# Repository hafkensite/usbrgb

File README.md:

# usbrgb

ATtiny85 based USB PCB that provides two WS2812B LED's, to be used as indicators.

# Hardware

The pcb design is based upon that of the [Digispark USB development board](http://digistump.com/products/1). For which they have released the [Eagle](https://s3.amazonaws.com/digistump-resources/files/3a5187f5_digispark_sources.zip) files.

The Digispark board uses an attiny84 microprocessor, which (with the help of some special software), can be programmed over USB once the bootloader is flashed once.

The width of the original Digispark pcb is slightly too wide to fit in some usb ports, when they are located at an edge. A fairly large part of the pcb is occupied by a voltage regulator. As the usbrgb PCB is to be used in a computer, there is no need for a 5Volt regulator.

Removing the regulator, and a few other non-critical components allowed the board to be narrower. I chose for a 'bigger' package for the passive components, as I want to solder it to manually.

## Layout

## Components

| Qty | Value      | Package | Parts  | Description                     |
| --- | ---------- | ------- | ------ | ------------------------------- |
| 1   | ATTINY85   | SOP8    | IC1    | Atmel ATTINY85-20SU             |
| 2   | 68R        | 1206    | R1, R2 | Resistor                        |
| 1   | 1K5        | 1206    | R3     | Resistor                        |
| 2   | 3.3v Zener | SOD-123 | D1, D2 | Diode                           |
| 1   | 4.7uf      | C1206   | C2     | Capacitor                       |
| 2   | WS2812B    | WS2812B | D3, D4 | WS2812B SMD addressable RGB LED |

# Embedded software

## Micronucleus bootloader
The [micronucleus](https://github.com/micronucleus/micronucleus) bootloader allows the Arduino IDE to program the chip over USB.

When the chip boots, it first presents itself as a usb device that can be programmed. After a short timeout the bootloader starts the Arduino code.

To flash the micronucleus bootloader you can use [avrdude](https://www.nongnu.org/avrdude/). I have programmed mine using an Arduino uno with the ISP sketch written to it.

## Arduino

To program the device using Arduino you can follow the steps describe in the [tutorial](http://digistump.com/wiki/digispark/tutorials/connecting).

> Note that the latest micronucleus version currently available (v2.04) is not supported by the Arduino plugin. I replaced the micronucleus application with the [latest version](https://github.com/micronucleus/micronucleus/tree/master/commandline), which works fine.

# Host software

The host application is written in Go, and uses the libusb interface to send control messages to the HID device. 

## Native messaging
The goal of this project is to be able to give a notification from within a browser. One of the ways to communicate from a browser to the host is using [native messaging](https://developer.mozilla.org/en-US/docs/Mozilla/Add-ons/WebExtensions/Native_messaging). This allows extensions to send messages to an executable on the host.

## Browser integration
The included firefox extension, together with the native-messaging application, allows the LED's to be set from within a web-page.

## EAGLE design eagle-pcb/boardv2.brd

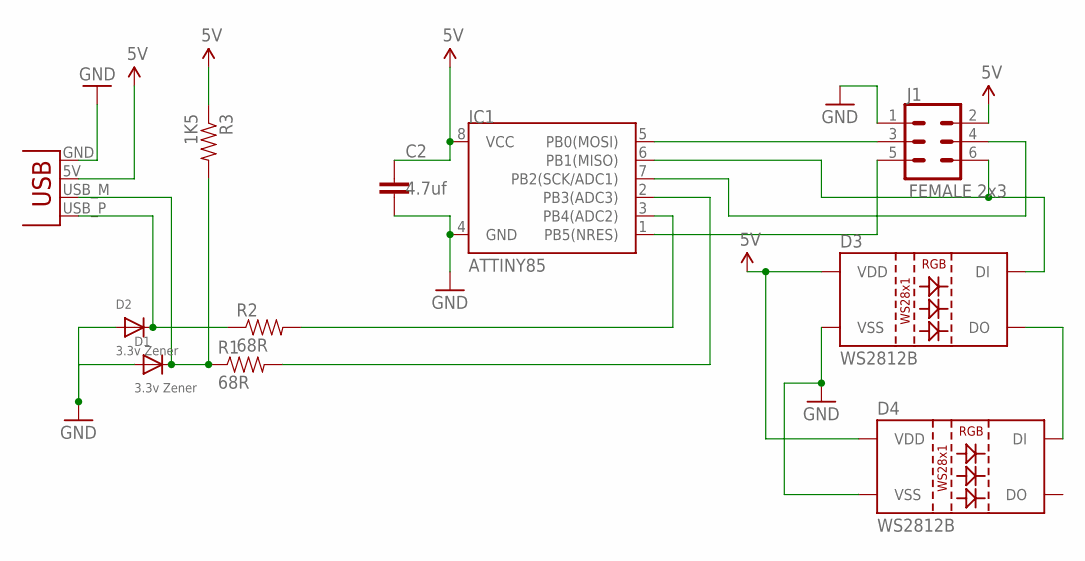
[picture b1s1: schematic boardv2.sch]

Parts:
C2: 4.7uf; C1206
D1, D2: 3.3v Zener; SOD-123
D3, D4: WS2812B
IC1: ATTINY85; SO08-EIAJ
J1: FEMALE 2x3; 2X3
R1, R2: 68R; 1206
R3: 1K5; 1206
X1: USBPCB; USB-A-PCB

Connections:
5V: C2.1, D3.1 (VDD), D4.1 (VDD), IC1.8 (VCC), J1.2, R3.1, X1.5V (VBUS)
GND: C2.2, D1.A, D2.A, D3.3 (VSS), D4.3 (VSS), IC1.4 (GND), J1.1, X1.GND
MISO: D3.4 (DI), IC1.6 (PB1(MISO)), J1.6
unnamed: D3.2 (DO), D4.4 (DI)
RESET: IC1.1 (PB5(NRES)), J1.5
SCK: IC1.7 (PB2(SCK/ADC1)), J1.4
SDA/MOSI: IC1.5 (PB0(MOSI)), J1.3
USB+: IC1.2 (PB3(ADC3)), R1.2
USB-: IC1.3 (PB4(ADC2)), R2.2
USB-M: D1.C, R1.1, R3.2, X1.USB_M (D-)
USB-P: D2.C, R2.1, X1.USB_P (D+)

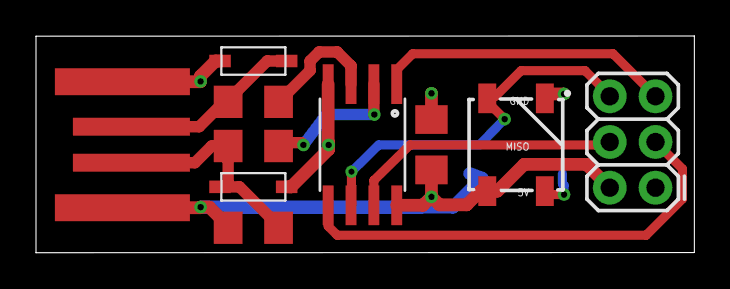
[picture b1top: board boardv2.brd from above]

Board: 2 copper layers, 36.6 x 12.0 mm, 11 parts (1 on the bottom side), 11 nets.

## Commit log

2020-07-26 Added eagle pcb files v1
2020-07-26 Added go app for browser native messaging
2020-07-26 Added arduino code for serial emulator
2020-07-26 Added micronucleus bootloader
2020-07-26 Remove backup eagle files, add images
2020-07-26 Readme v1
2020-07-26 Added basic firefox addon
2020-07-26 Add firefox extension to the readme
2020-07-26 FIX pcb, use MOSI to drive LED, not RESET
2020-08-02 Added photo, updated extension and go-app

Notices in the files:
parts and their libraries:
SparkFun: Licensing: CC v3.0 Share-Alike You are welcome to use this library for commercial purposes.
SparkFun-LED: Licensing: Creative Commons ShareAlike 4.0 International - https://creativecommons.org/licenses/by-sa/4.0
